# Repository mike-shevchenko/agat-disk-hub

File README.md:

# agat-disk-hub

KiCad project of an adapter PCB for connecting up to 3 140K floppy drives to Agat and Apple2 computers.

KiCad-проект платы-переходника для подключения до 3-х дисководов 140К к компьтютерам Агат и Apple2.

Шрифт Агата, использованный для текстов на передней маске платы - в [GitHub-проекте ретро-шрифтов](https://github.com/mike-shevchenko/retro-tools/tree/master/fonts)

Фото платы и материалы для производства - в разделе [Releases](https://github.com/mike-shevchenko/agat-disk-hub/releases)

---------------------------------------------------------------------------------------------------
## Использование платы

Плата agat-disk-hub позволяет подключить к компьютерам Агат и Apple2 от одного до трех дисководов или их эмуляторов на 140 КБ, с возможностью на ходу выбирать, какой из них будет первым, а какой - вторым.

Плата хаба представляет собой пассивных переходник, нужным образом соединяющий все контакты разъемов. Единственная радиодеталь - резистор для светодиодов, если вместо джамперов выбора 1/2 дисководов захочется подключить панель с тумблерами и светодиодами.

С помощью единственного разъема, установленного на задней стороне платы хаба, она надевается на дисковод Изот вместо кабеля от контроллера дисковода, с возможностью дополнительной фиксации с помощью штатной или иной пружинной скобы, проволоки, стяжек или винтов М3. Если дисковод Изот подключать не нужно, то можно использовать плату хаба на весу как переходник для подключения других дисководов.

### Подключение к контроллеру дисковода

Из двух соседних разъема на передней стороне, обозначенных как **КОНТРОЛЛЕР**, используется **только один,** в зависимости от имеющегося кабеля - верхний предназначен для штатного кабеля Агата от контроллера к дисководу Изот, нижний - для кабеля, изготовленного по стандарту Apple2, в т.ч. прямого шлейфа на 20 жил от компьютера Apple2.

Если нужно подключить более одного дисковода, то в дополнение к одному из описанных выше кабелей нужно дополнительно подключить один провод с сигналом выбора второго дисковода. Этот сигнал присутствует на разъеме контроллера Агата на контакте **B7** (в среднем ряду), и в штатном кабеле Агата не подключен, поэтому можно припаять провод либо надеть неразношенное гнездо Dupont (BLS-1) на его хвостовик. У контроллера Apple2 имеется два запараллеленных разъема для дисководов, отличающихся только одним контактом **14** выбора дисковода, поэтому нужный сигнал можно взять также проводом Dupont со второго разъема контроллера. На плату хаба этот сигнал приводится на отдельно стоящий штырь **ВБ2** ("Выбор Блока 2" - обозначение по схеме Агата).

Если не использовать штатный кабель Агата, то можно изготовить кабель для подключения к контроллеру Агата следующим способом. Понадобится разъем СНП34[С]-30В - вилка, подключающаяся к контроллеру, необязательная буква [С] означает посеребреные контакты вместо позолоченных, подойдут любые. Можно взять шлейф из 14 или более, до 21, жилы и припаять к разъему, или столько же проводов Dupont с неразношенными гнездами надеть на хвостовики разъема. На другой конец шлейфа обжимаем IDC-20, отделив провод с сигналом ВБ2 на отдельное гнездо Dupont (BLS-1), либо, если это провода Dupont, перенести их контакты кроме ВБ2 в общее гнездо BLD-10. Удобно использовать шлейф на 20 жил, переназначив жилу 1 (коричневая в многоцветном шлейфе) под ВБ2 вместо земли, так как трех или даже двух жил для земли вполне достаточно - со стороны хаба эту жилу не нужно заводить в IDC-20, а нужно отделить примерно на 30 мм и обжать или припаять на нее Dupont (BLS-1). Схема распайки кабеля:

```
  Вид на розетку в контроллере (СНП34-30):       Вид на штыри на плате (IDC-20):
    1   2   3   4   5   6   7   8   9  10          2   4   6   8  10  12  14  16  18  20
   _-------------------------------------_       -----------------------------------------
C |GND  .  +12 Ф0D Ф1C Ф2B Ф3A +5   . [-12] C    |Ф0D Ф1C Ф2B Ф3A ЗПС +5  ВБ  ДСЧ ДЗП ЗЗП|
B | .   .   .   .   .   .  ВБ2  .   .   . | B    [GND]GND GND GND[-12]+5  +12 +12 +12 +12|
A |ДСЧ ЗЗП  .  ЗПС  .   .   .  ВБ  ДЗП GND| A    --------^----------___--------------^----
  -----------------------------------------        1   3   5   7   9  11  13  15  17  19
    1   2   3   4   5   6   7   8   9  10
```
Провод -12 нужно подключать, только если планируется использовать дисковод Apple 2 - дисковод Изот и эмуляторы дисководов это напряжение не используют. Если планируется подключать только эмуляторы дисководов, то можно также не подключать +12 - им достаточно +5. При использовании стандартного шлейфа желательно припаять к соответствующим выводам СНП34-30 все одноименные провода, за возможным исключением одного из четырех проводов земли, который можно задействовать для ВБ2. Если же вместо шлейфа использовать провода Dupont (они обычно имеют большее сечение), можно ограничиться одним на каждый сигнал, подведя его в любой точке с нужным наименованием.

### Подключение к дисководам

Тут все очень просто, ведь для этого хаб и существует.

На дисковод Изот плата хаба просто надевается. В зависимости от типа распаянного на задней стороне платы разъема, можно дополнительно зафиксировать плату на дисководе штатной или самодельнолй пружинной скобой, винтами M3, проволокой или нейлоновыми стяжками, используя отверстия в плате, которые располагаются точно напротив отверстий разъема на дисководе.

Для подключения дисковода от Apple2 достаточно использовать простой шлейф с разъемами IDC-20, с прямым соединением, подключаемым к разъему хаба **A-APPLE2**. Также подключается и эмулятор дисковода **"SDISK//"** (на базе микроконтроллера Atmega, с SD-картой), в народе известный как "японский".

Для подключения эмуляторов дисковода типа Gotek также используется простой шлейф с разъемами IDC-34, с прямым соединением - можно использовать стандартный шлейф дисковода IBM PC или Beta Disk (TR-DOS), но только его пару разъемов без перекруток. Сами Gotek нужно настроить джамперами и проводами-перемычками, и прошить прошивкой с поддержкой режима Apple2, как указано в [GitHub-проекте этих прошивок](https://github.com/mike-shevchenko/flashfloppy)

Для питания Gotek от платы хаба можно использовать разъем **ВЫХОД** - это стандартный разъем, как для вентиляторов на материнских платах, но вместо тахометра и ШИМ на него выведены земля и +5 В (остальные 2 контакта - земля и +12 В - оставлены на своих местах). Можно изготовить кабель с такого разъема на разъем питания дисковода 3.5'' (его называют Berg), или использовать провода Dupont - для Gotek достаточно только двух проводов: земля и +5.

### Выбор дисковода

Контроллеры Агата и Apple2 поддерживают два дисковода. При выборе в программе первого дисковода будет работать тот, на который подведен сигнал ВБ1, второго - ВБ2. В момент, когда дисководы не работают, можно смело перекоммутировать эти сигналы, таким образом, выбирая, какой дисковод будет первым, а какой вторым при следующем обращении.

Для назначения любого из двух или трех подключенных дисководов первым, а другого - вторым (третий при этом не будет задействован), на плате хаба предусмотрен блок штырей **ВБ**. Можно как замкнуть нужные контакты в блоке джампером, так и присоединить к этим штырям 10-жильный шлейф, и собрать блок тумблеров и светодиодов. Незадействованные джамперы можно хранить на штырях **ДЕРЖ.ДЖ.**.

Справа от блока напечатана подсказка, какие контакты нужно замыкать: буква обозначает разъем дисковода - `И`, `A`, `G`; цифры `1` и `2` обозначают сигналы выбора дисковода ВБ1 и ВБ2. Нужно соединить каждую цифру с нужной буквой.

Дополнительные штыри в блоке - земля и вывод +5 В через резистор (`L`) - могут быть полезны при устройстве панели с тумблерами, чтобы подключать ее единственным шлейфом чисто к плате хаба.

---------------------------------------------------------------------------------------------------
## Сборка платы хаба

### Разъемы к дисководу Изот

Это пара разъемов польской фирмы Eltra, в продаже найти нереально, советский/современный аналог не известен. Двурядный с шагом 2.5. По расположению и размеру контактов обе части совместимы с советскими СНО/СНП, но корпуса не подходят. Идеальный вариант - изотовление корпусов разъемов, снаружи идентичных Eltra, и установка в них гнезд и штырей от советского разъема СНП58 или СНО53.

Альтернативы для разъема к дисководу (XS1, "И-ИЗОТ"):

- Запаять на плату розетку Yxcon F168-1215A0BSQC3 - двурядная 2.54; нужно будет подпилить её напильником с боков до ширины розетки Eltra (34.1), и пропилить пазы в корпусе до толщины 5.3. Конструкция его гнезд позволяет состыковаться со штырями на дисководе. Отверстия в плате расширены для принятия шага 2.54 в дополнение к 2.5.

- Хорошо подходят к штырям Eltra гнезда от Dupont (BLS), но только ДО первого надевания на стандартные штыри 0.64 (после него начинают болтаться на узких штырях Eltra). Можно обжать или припаять в контакты BLS кусочки короткого толстого неизолированного провода типа от витой пары, и запаять в плату после надевания на разъём дисковода (это важно, чтобы контакты встали в правильное положение, обхватив штыри ответной части).

Альтернатива для разъема к штатному шлейфу от контроллера дисковода:

- Можно использовать комбинацию из запаянного на плату IDC-26 (или штырей BLD-13), на который надевается розетка PBD-30, хвостовики которой хорошо входят в розетку Eltra. Для исключения смещения по ширине можно напаять на крайние пары хвостовиков поперечные перемычки, например, из пина PBD (толщина 0.4). Для исключения вставки не той стороной можно наклеить на PBD две пластины толщиной 0.5 или 0.6 на двустороннюю ленту толщиной 0.2 (3M GPT 020F), в форме буквы П - пара выступов на каждой пластине будет попадать в пропилы.

### Контакты ВБ

Рекомендуется запаять IDC-10, для однозначного присоединения шлейфа панели тумблеров. Если планируется исключительно установка джамперов, можно просто запаять блок штырей.

Резистор для светодиодов: если не планируется подключать самодельные светодиоды индикации выбранного дисковода, то его можно не запаивать. Типичное значение, позволяющее запитать один или два светодиода - 680 Ом 0.5 Вт. При желании можно припаять SMD-резистор 1205 с задней стороны платы, а также закоротить площадки резистора, если на панель тумблеров требуется подать +5 В напрямую. ВНИМАНИЕ: В этом варианте есть опасность надевания джампера на +5 и один из выходов ВБ, что может привести к выходу из строя контроллера дисковода - именно поэтому на плате предусмотрен резистор, который от этого защищает.

### Разъемы Gotek

Разъем Gotek IDC-34: перед монтажом нужно удалить контакт 5, он является традиционным механическим ключом - существуют стандартные шлейфы, где этот контакт заглушен, поэтому в плате под него не предусмотрено отверстие.

Контакт IDC-34.32 также получает сигнал PH1 от дорожки на обратной стороне платы, идущей к IDC-34.16 - это нужно для обспечения совместимости с [прошивкой Gotek "307" от Олега Одинцова](https://agat-hardware.sourceforge.io/agat-gotek-140k.html) Если ее поддержка не предполагается, и это соединение по каким-то причинам нежелательно, это ответвление дорожки на IDC-34.32 можно отрезать.

В качестве разъема питания Gotek можно установить как 4-х, так и 3-х и даже двухконтактный разъем, так как нужны только контакты земли и +5. Рекомендуется установить полный 4-контактный разъем как для вентилятора на материнской плате, с язычков шириной в 3 контакта, и изготовить кабель с ответной частью к нему (разъем от вентилятора) на разъем питания 3''-дисковода (его обычно называют Berg); в таком кабеле достаточно иметь два провода - будет меньше шансов неправильно подключить контакты и повредить Gotek.

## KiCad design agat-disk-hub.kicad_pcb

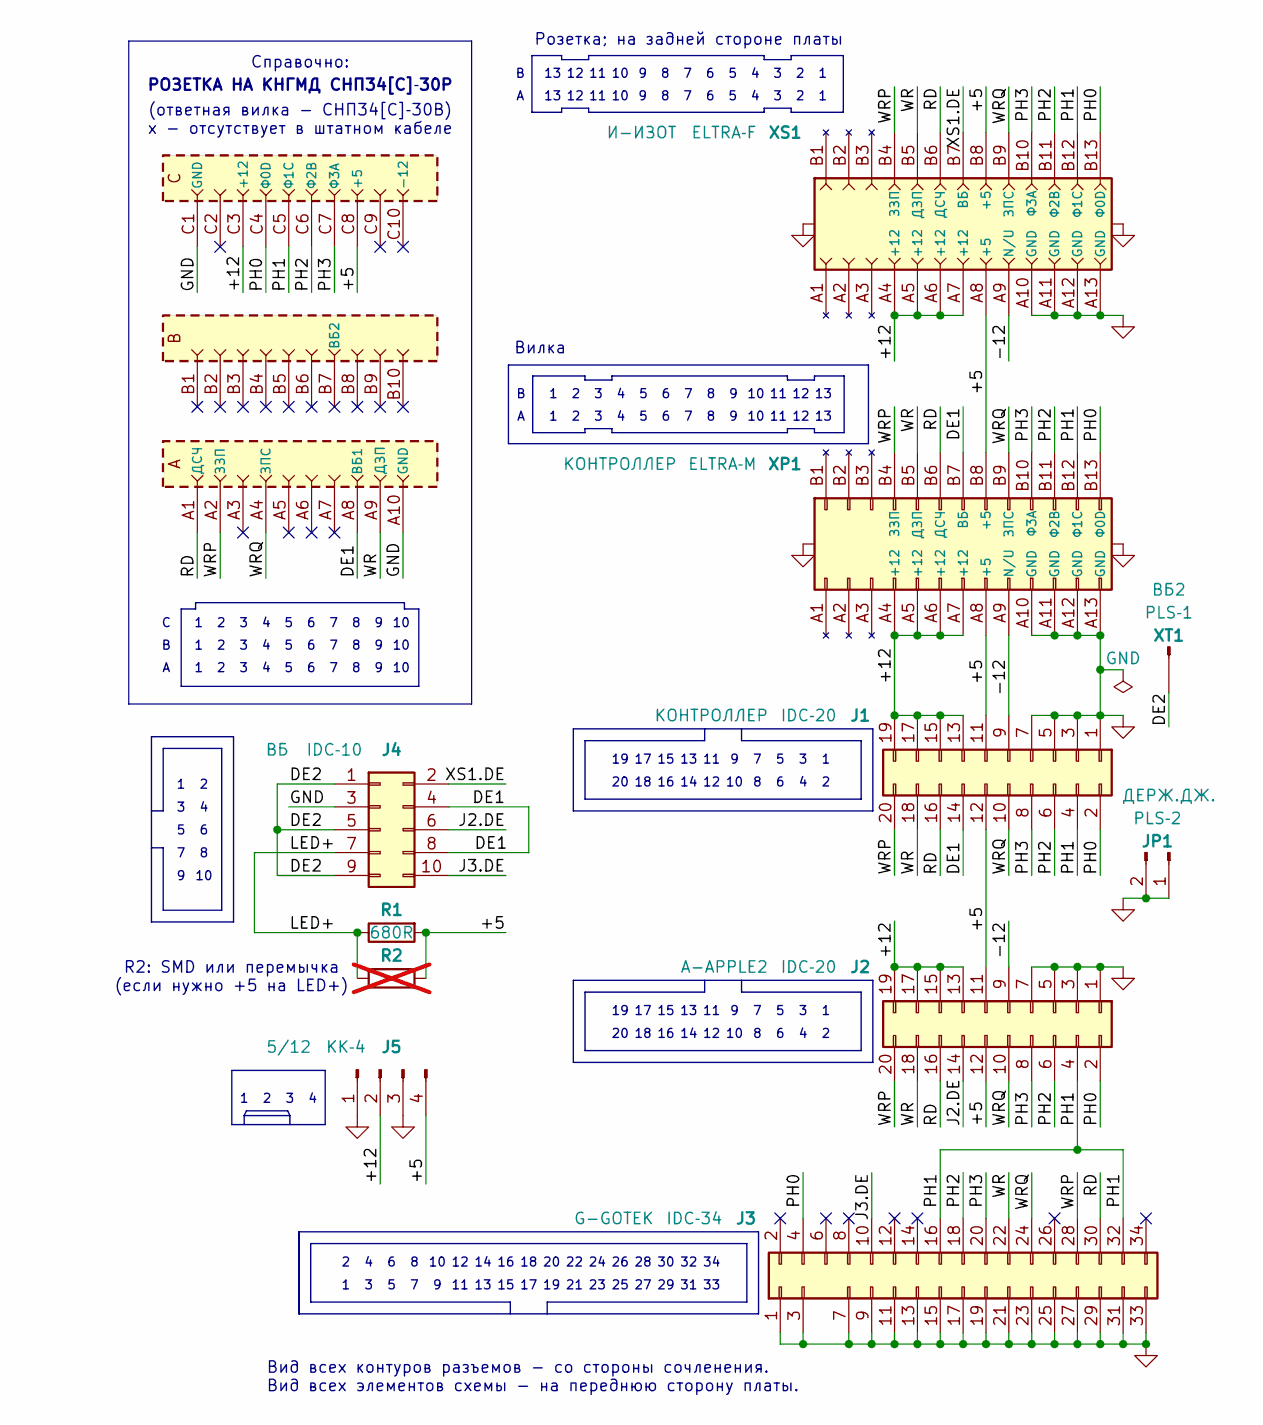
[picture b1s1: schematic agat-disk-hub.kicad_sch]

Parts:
J1, J2: IDC‐20; IDC-20_header_vertical_rotation180
J3: IDC‐34; IDC-34_header_vertical_rotation0
J4: IDC‐10; IDC-10_header_vertical_rotation270
J5: KK‐4; Molex_KK-4_vertical_rotation0
JP1: PLS‐2; PinHeader_1x02_P2.54mm_Vertical
R1: 680R; R_Axial_DIN0207_L6.3mm_D2.5mm_P10.16mm_Horizontal
R2: 0R; jumper_1206_solder_drop; not fitted
XP1: ELTRA‐M; Eltra-26M
XS1: ELTRA‐F; Eltra-26F
XS404: СНП34-30Р; СНП34С-30
XT1: PLS‐1; PinHeader_1x01_P2.54mm_Vertical

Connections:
/+5: J1.11, J1.12, J2.11, J2.12, J5.4, R1.2, R2.1, XP1.A8 (+5), XP1.B8 (+5), XS1.A8 (+5), XS1.B8 (+5), XS404.C8 (+5)
/+12: J1.13, J1.15, J1.17, J1.19, J2.13, J2.15, J2.17, J2.19, J5.2, XP1.A4 (+12), XP1.A5 (+12), XP1.A6 (+12), XP1.A7 (+12), XS1.A4 (+12), XS1.A5 (+12), XS1.A6 (+12), XS1.A7 (+12), XS404.C3 (+12)
/-12: J1.9, J2.9, XP1.A9 (N/U), XS1.A9 (N/U)
/DE1: J1.14, J4.4, J4.8, XP1.B7 (ВБ), XS404.A8 (ВБ1)
/DE2: J4.1, J4.5, J4.9, XT1.1 (Pin_1_1)
/J2.DE: J2.14, J4.6
/J3.DE: J3.10, J4.10
/LED+: J4.7, R1.1, R2.2
/PH0: J1.2, J2.2, J3.4, XP1.B13 (Ф0D), XS1.B13 (Ф0D), XS404.C4 (Ф0D)
/PH1: J1.4, J2.4, J3.16, J3.32, XP1.B12 (Ф1C), XS1.B12 (Ф1C), XS404.C5 (Ф1C)
/PH2: J1.6, J2.6, J3.18, XP1.B11 (Ф2B), XS1.B11 (Ф2B), XS404.C6 (Ф2B)
/PH3: J1.8, J2.8, J3.20, XP1.B10 (Ф3A), XS1.B10 (Ф3A), XS404.C7 (Ф3A)
/RD: J1.16, J2.16, J3.30, XP1.B6 (ДСЧ), XS1.B6 (ДСЧ), XS404.A1 (ДСЧ)
/WR: J1.18, J2.18, J3.22, XP1.B5 (ДЗП), XS1.B5 (ДЗП), XS404.A9 (ДЗП)
/WRP: J1.20, J2.20, J3.28, XP1.B4 (ЗЗП), XS1.B4 (ЗЗП), XS404.A2 (ЗЗП)
/WRQ: J1.10, J2.10, J3.24, XP1.B9 (ЗПС), XS1.B9 (ЗПС), XS404.A4 (ЗПС)
/XS1.DE: J4.2, XS1.B7 (ВБ)
GND: J1.1, J1.3, J1.5, J1.7, J2.1, J2.3, J2.5, J2.7, J3.1, J3.3, J3.7, J3.9, J3.11, J3.13, J3.15, J3.17, J3.19, J3.21, J3.23, J3.25, J3.27, J3.29, J3.31, J3.33, J4.3, J5.1, J5.3, JP1.1, JP1.2, XP1.A10 (GND), XP1.A11 (GND), XP1.A12 (GND), XP1.A13 (GND), XP1.SCREW_L, XP1.SCREW_R, XS1.A10 (GND), XS1.A11 (GND), XS1.A12 (GND), XS1.A13 (GND), XS1.SCREW_L, XS1.SCREW_R, XS404.A10 (GND), XS404.C1 (GND)

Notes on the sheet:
Розетка; на задней стороне платы
Справочно:
(ответная вилка - СНП34[С]‐30В) х - отсутствует в штатном кабеле
Вилка
РОЗЕТКА НА КНГМД СНП34[С]‐30Р
Вид всех контуров разъемов - со стороны сочленения. Вид всех элементов схемы - на переднюю сторону платы.
R2: SMD или перемычка (если нужно +5 на LED+)

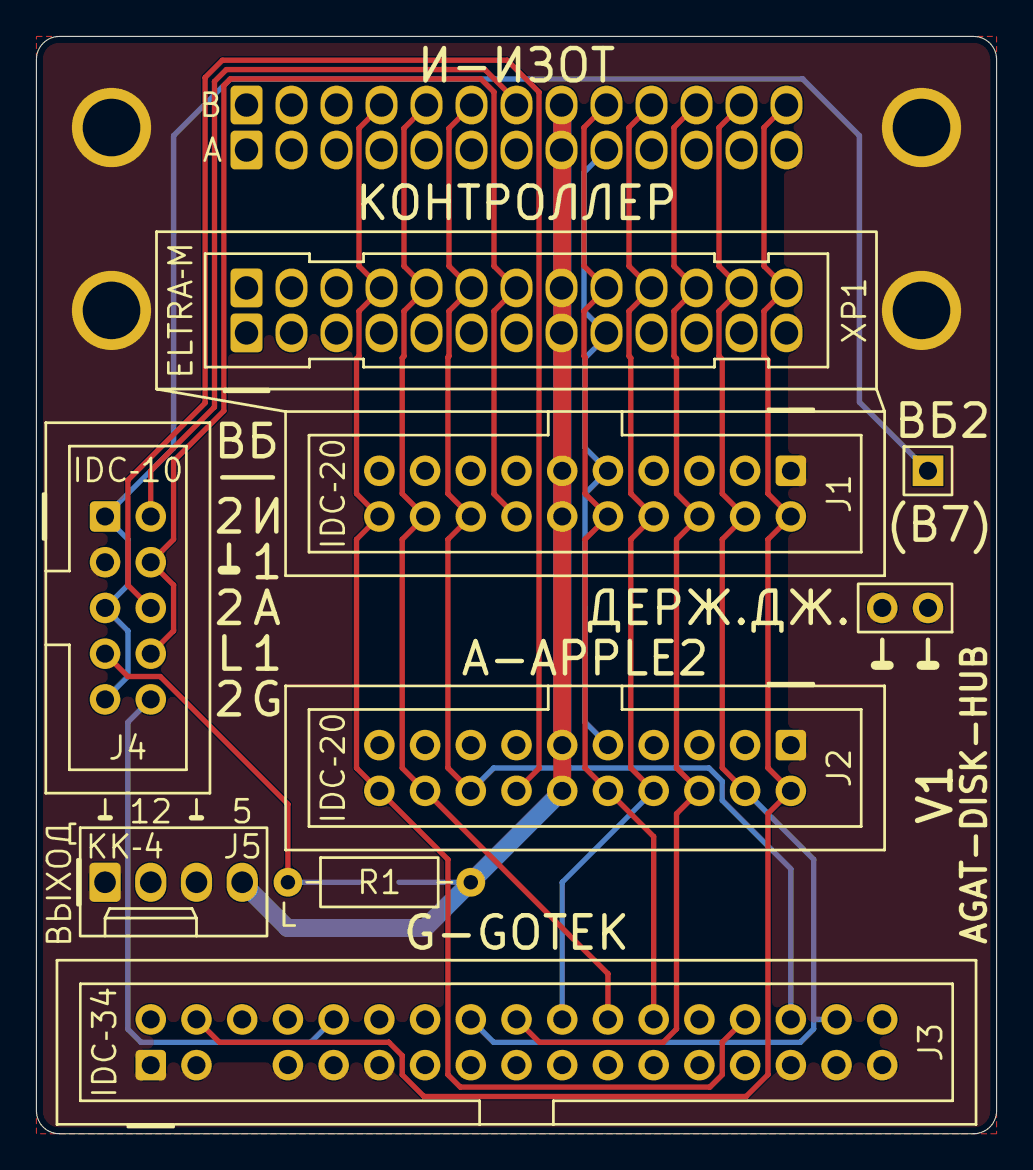
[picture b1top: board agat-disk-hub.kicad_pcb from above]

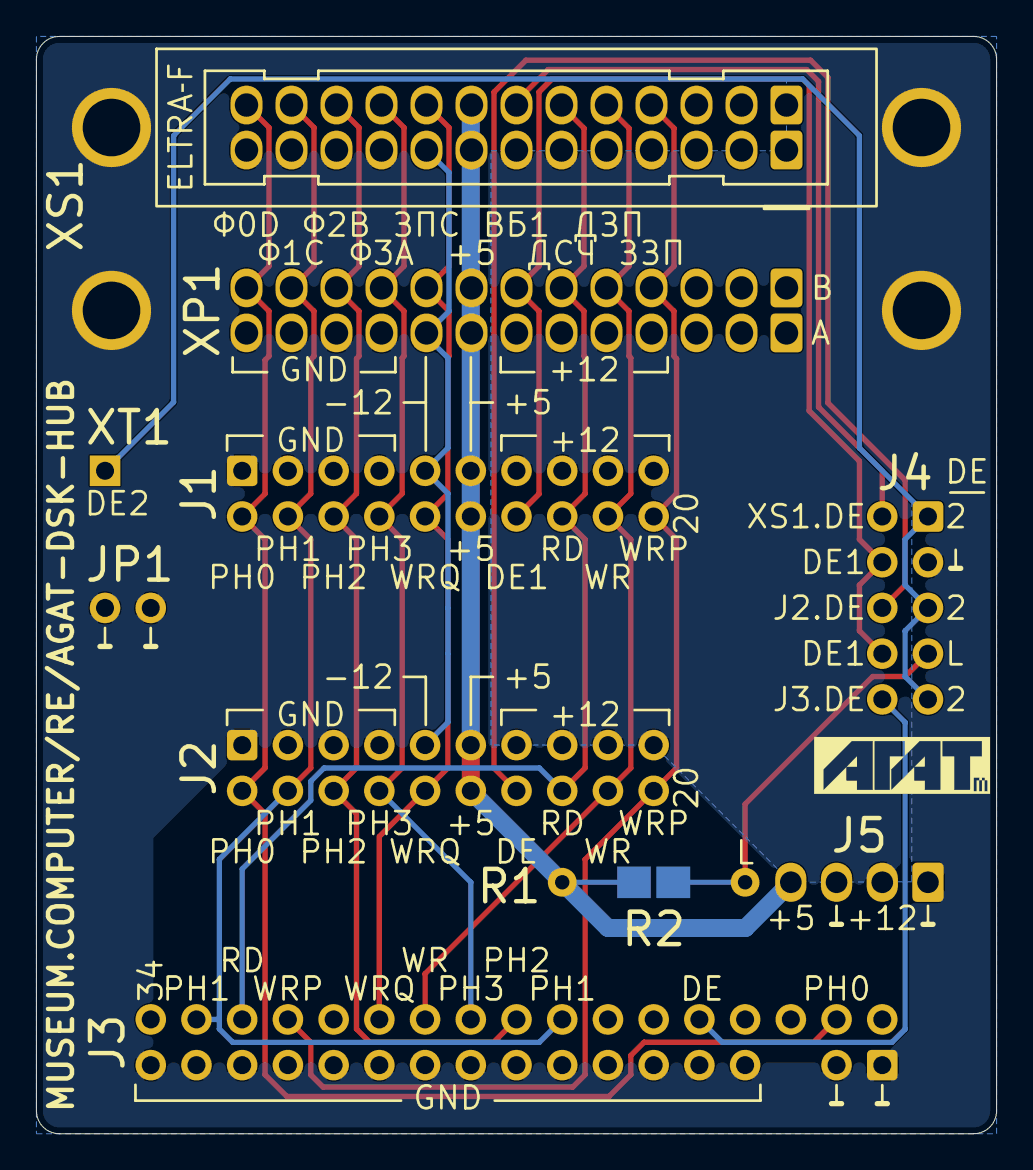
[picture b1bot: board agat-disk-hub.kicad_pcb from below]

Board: 2 copper layers, 53.3 x 61.0 mm, 11 parts (2 on the bottom side), 18 nets.
